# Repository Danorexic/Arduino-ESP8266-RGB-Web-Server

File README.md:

# Arduino-ESP8266-RGB-Web-Server-FastLED
A Wi-Fi web server for the ESP8266 platform driving a WS2812B addressable RGB Led strip - Arduino sketch

Description:
An Arduino sketch for running a Wi-Fi web server on the ESP8266-12F. Designed to drive the WS2812B addressable RGB Led strips using the FastLED Arduino library.

Updates:
I have now implemented brightness and color controls that is usable via Adafruit IO. For my setup at home, I use a toggle button for the on/off, a slider for brightness, and a textbox for the color commands. Casing not matter for the color and on/off commands. Valid brightness numbers are 0-100 and are mapped to the 0-255 the program uses. 
I've also included some photos in the photos folder of my Adafruit IO dashboard and how I've setup some of my IFTTT applets. 

Construction Notes:
This repository contains the Arduino program, HTML pages, and associated Eagle schematic and board design files. This project is forked from Giznoise's GitHub repo which I've modified extensively. I wanted to create a lightbox for my girlfriend and was able to control LED's with my Arduino but had no idea how to get them to be controlled via a webpage. Giznoise's project had this implemented wonderfully and I made adjustments along the way. I've reworked a fair bit of their program and added various features, libraries, and more. 

Changes include:
1) Changing the LED control library from Adafruit's Neopixel to the FastLED library.
2) Improving the look of the web control pages and making them better able to adjust to different screen sizes.
3) Swapping the HTML5 color picker to the JSColor javascript library. iOS devices did not support the HTML5 color picker. 
4) Adding additional web control settings to support changing blending modes, choosing different patterns, etc.
5) Added Google Assistant control support throught IFTT and Adafruit IO.
6) Created a schematic and board layout in Eagle that supports dropping in a NodeMCU v2 for controls.
7) Using a SN74AHCT125D level shifter in the schematic to enable the NodeMCU to better control the WS2812b strips. The strips need 5v signal logic and the NodeMCU provides 3.3v; this IC addresses this issue.
8) Adds Android OTA support which enables you to easily upload new programs to the NodeMCU/ESP8266 board without having to use a USB cable. 

Useful Information:
You will need to utilize the ESP8266 uploader tools to upload the data folder. You don't have to do anything special, just follow the directions for installing the tool, and just click tools, ESP8266 Sketch Data Upload and it will upload the needed files. This allows the JScolor.js file to be hosted locally on the ESP8266 vs having to host it online. A link to this tool is provided at the bottom of this page. 

Possible issues and features missing from the original project:

1) Candle mode was not converted to the FastLED library. 
2) It can be accessed via IP or via mDNS by devices on the same wifi network by typing lightbox.local in the address bar - However this feature does not function in Chrome on Android or iOS. It works in Safari on iOS and Chrome for Windows. In the future it may be possible to announce the IP address via the MQTT client but this is not implemented. The original author had similar issues and recommended finding the IP via your router admin panel. 
3) Present board design hosted on GitHub is a revision of the one I had originally gotten fabricated and has not been fabricated and tested again. It should work without issue as I only made some small tweaks to improve the board's layout.
4) The board and schematic allow for 4 LED strips to be connected but the program only supports one. I have not tested function of terminals 2-4 as of yet. The extra 3 were implemented as a future expandability option.
5) The holes for the headers for the NodeMCU to drop into are spaced according to the NodeMCU Eagle library but most NodeMCU devboard pins sort of bow out a bit. I had to bend the pins on my devboards to make them align better. 

Items to be improved:

1) A method to announce the board's IP address, likely through the MQTT client.
2) Improving the board design to directly implement an actual ESP8266 or ESP32 chip vs dropping in a NodeMCU v2 devboard. Dropping in the devboard was far easier for me to get the board design tested and up and running. 
3) Updating board design to allow for both 2.54mm and 3.5mm 3 position screw terminals, similar to how the Big Easy stepper driver allows for both sizes. 
4) Improving board design to utilize more SMD components where possible. 
5) An ESP32 version of this design for the future may be nice. 
6) Potentially splitting up the html_pages.h file into separate html pages now that I know how to store and read files from the SPIFFS.

Implements the following:

FastLED library:
https://github.com/FastLED/FastLED

Pubsubclient (MQTT) for the Google Assistant control:
https://github.com/knolleary/pubsubclient

ESP8266 Web Server:
https://github.com/esp8266/Arduino/blob/master/libraries/ESP8266WebServer/examples/AdvancedWebServer/AdvancedWebServer.ino

Using the onboard SPIFFS to store the JScolor library:
https://tttapa.github.io/ESP8266/Chap11%20-%20SPIFFS.html

ESP8266fs uploader tool:
https://github.com/esp8266/arduino-esp8266fs-plugin

JSColor javascript color picker:
http://jscolor.com/

Special thanks to:
* The original author's hard work.
* This Reddit post and guide for showing how to fix the flickering issues by using the level shifting IC:
https://www.reddit.com/r/esp8266/comments/4v24c1/d1_mini_level_converter_2812b_led_power_supply/
https://happyinmotion.com/?p=1247
* This guide on how to use Google Assistant in conjunction with IFTTT and Adafruit IO:
http://www.instructables.com/id/Control-Your-Projects-With-Google-Assistant-and-Ad/
* Countless other users on StackExchange, the Arduino Forums, and other websites whose questions and answers helped me along the way. 
* This guide on using multiple MQTT topics:
https://www.baldengineer.com/multiple-mqtt-topics-pubsubclient.html

A bill of materials for Digikey is also provided within this repository. 

Demo video viewable here: https://youtu.be/otg-TUXe8Jg

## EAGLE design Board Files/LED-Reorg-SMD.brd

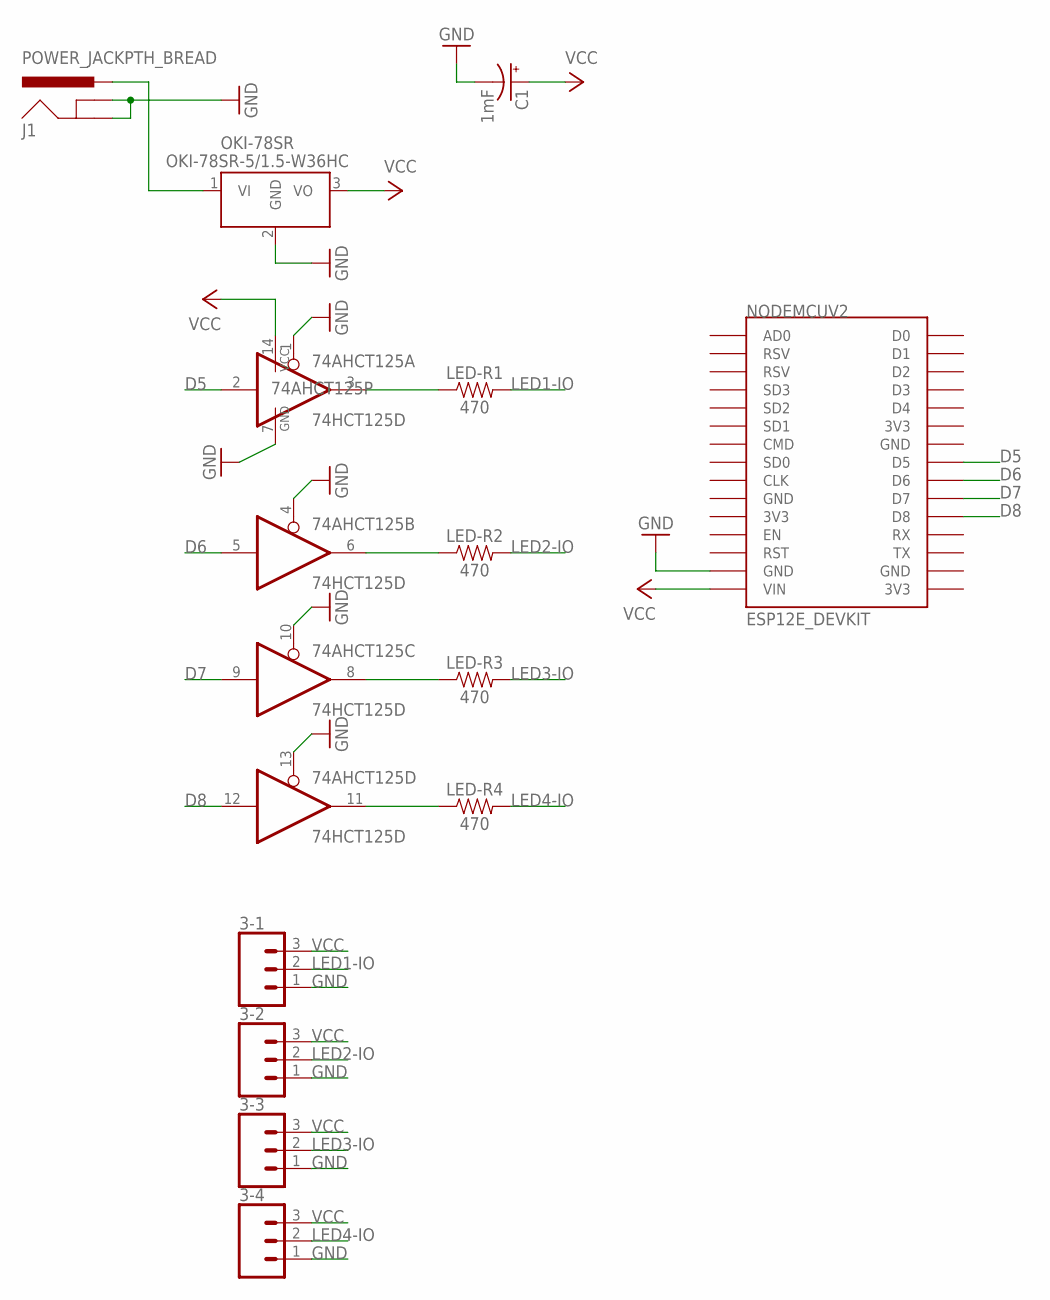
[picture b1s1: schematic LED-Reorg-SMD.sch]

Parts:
3-1, 3-2, 3-3, 3-4: CONN_03SCREW; SCREWTERMINAL-3.5MM-3
74AHCT125: 74HCT125D; SO14
C1: 1mF; CPOL-RADIAL-5MM-10MM
J1: POWER_JACKPTH_BREAD; POWER_JACK_PTH_BREAD
LED-R1, LED-R2, LED-R3, LED-R4: 470; 1206
NODEMCUV2: ESP12E_DEVKIT
OKI-78SR: OKI-78SR-5/1.5-W36HC; OKI-78SR_HORIZ

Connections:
D5: 74AHCT125.2 (I), NODEMCUV2.D5
D6: 74AHCT125.5 (I), NODEMCUV2.D6
D7: 74AHCT125.9 (I), NODEMCUV2.D7
D8: 74AHCT125.12 (I), NODEMCUV2.D8
GND: 3-1.1, 3-2.1, 3-3.1, 3-4.1, 74AHCT125.1 (OE), 74AHCT125.4 (OE), 74AHCT125.7 (GND), 74AHCT125.10 (OE), 74AHCT125.13 (OE), C1.-, J1.GND, J1.GNDBREAK, NODEMCUV2.GND@1 (GND), OKI-78SR.2 (GND)
LED1-IO: 3-1.2, LED-R1.2
LED2-IO: 3-2.2, LED-R2.2
LED3-IO: 3-3.2, LED-R3.2
LED4-IO: 3-4.2, LED-R4.2
unnamed: 74AHCT125.3 (O), LED-R1.1
unnamed: 74AHCT125.6 (O), LED-R2.1
unnamed: 74AHCT125.8 (O), LED-R3.1
unnamed: 74AHCT125.11 (O), LED-R4.1
unnamed: J1.PWR, OKI-78SR.1 (VI)
VCC: 3-1.3, 3-2.3, 3-3.3, 3-4.3, 74AHCT125.14 (VCC), C1.+, NODEMCUV2.VIN, OKI-78SR.3 (VO)

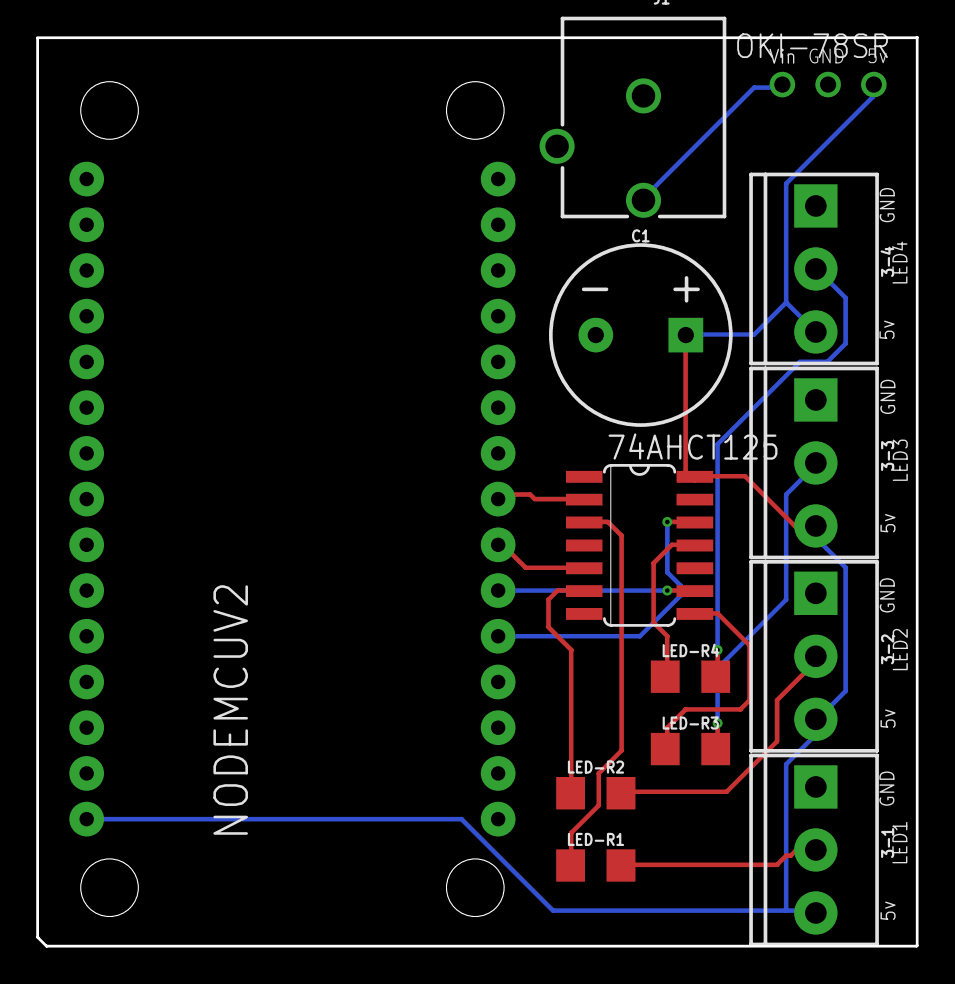
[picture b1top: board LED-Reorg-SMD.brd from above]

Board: 2 copper layers, 48.9 x 50.5 mm, 13 parts (0 on the bottom side), 15 nets.

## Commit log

2018-07-17 Pushing current revision
    Initial release of forked project
2018-07-17 Renaming files
    Renaming files to that .INO matches folder name to comply with Arduino compile requirements.
2018-07-17 Including photos
    Attaching photos of fabricated PCB
2018-07-17 Demo video
    Included link to demo video in Readme.
2018-07-17 ESP8266 File Upload Tool
    Mentioned the link at the bottom of the page for uploading the data folder to the board's SPIFFS.
2018-07-17 Additional Photos
    Included additional photos
2018-07-25 Brightness and color controls via voice added
    Program now provides additional topics for Adafruit IO that should allow users to control the brightness and colors with their voice. Included some photos of how things are setup in IFTTT and Adafrui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

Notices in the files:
parts and their libraries:
SparkFun-Capacitors: Licensing: Creative Commons ShareAlike 4.0 International - https://creativecommons.org/licenses/by-sa/4.0
